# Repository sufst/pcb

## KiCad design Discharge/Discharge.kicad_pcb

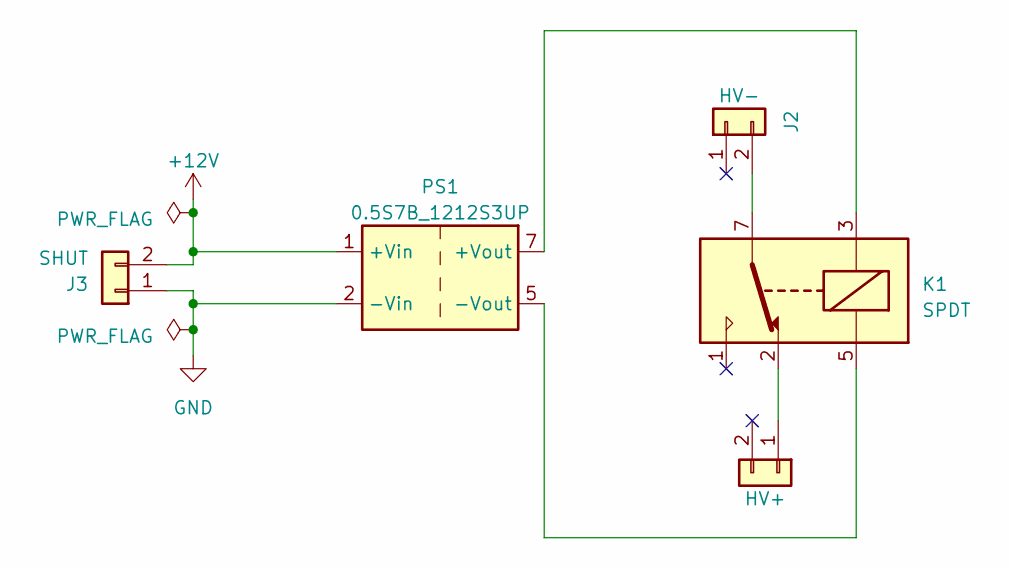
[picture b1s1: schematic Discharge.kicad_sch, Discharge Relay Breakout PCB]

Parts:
J1: HV+; Molex_Micro-Fit_3.0_43650-0200_1x02_P3.00mm_Horizontal
J2: HV-; Molex_Micro-Fit_3.0_43650-0200_1x02_P3.00mm_Horizontal
J3: SHUT; Molex_Micro-Fit_3.0_43650-0215_1x02_P3.00mm_Vertical
K1: SPDT; pickering-67-1-c
PS1: 0.5S7B_1212S3UP

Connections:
+12V: J3.2, PS1.1 (+Vin)
GND: J3.1, PS1.2 (-Vin)
unnamed: J1.1, K1.2
unnamed: J2.2, K1.7
unnamed: K1.3, PS1.7 (+Vout)
unnamed: K1.5, PS1.5 (-Vout)

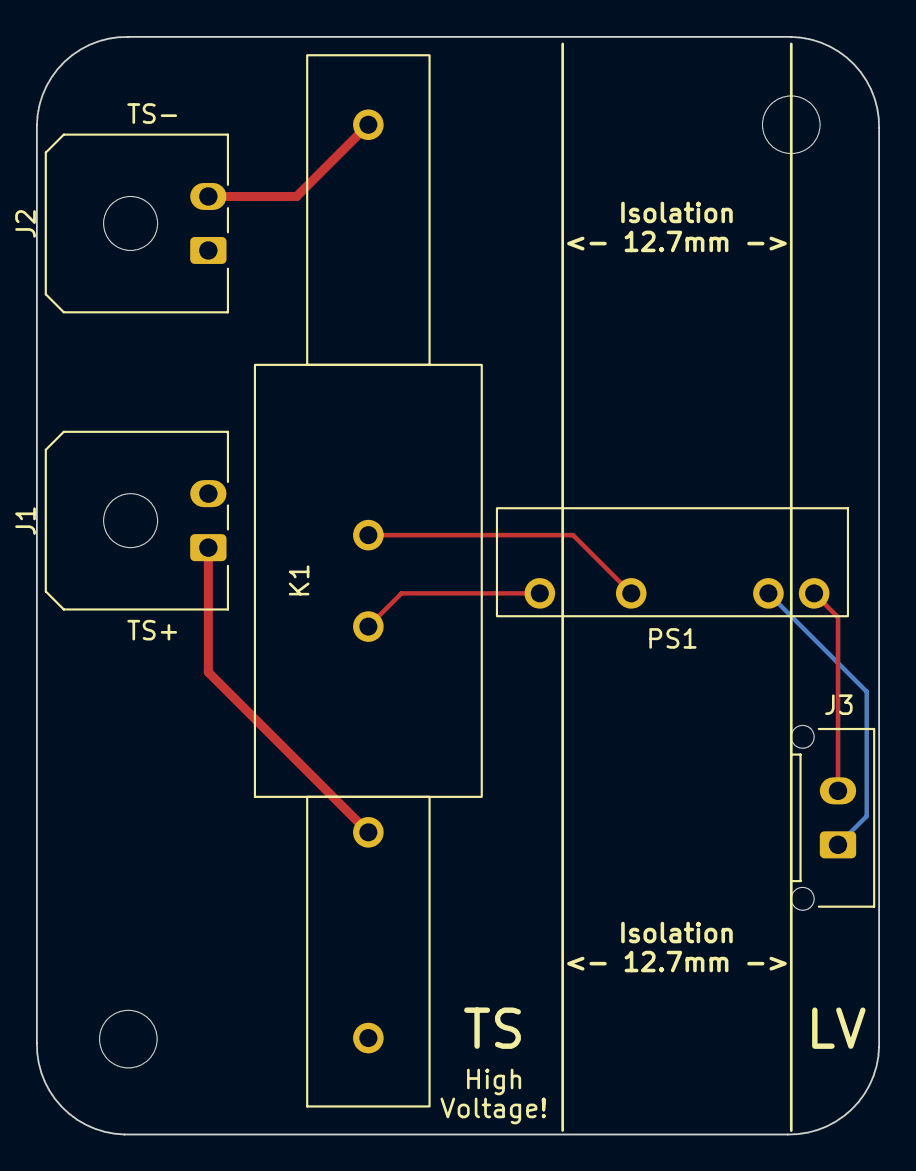
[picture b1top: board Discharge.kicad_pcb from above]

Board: 2 copper layers, 46.8 x 61.0 mm, 5 parts (0 on the bottom side), 6 nets.

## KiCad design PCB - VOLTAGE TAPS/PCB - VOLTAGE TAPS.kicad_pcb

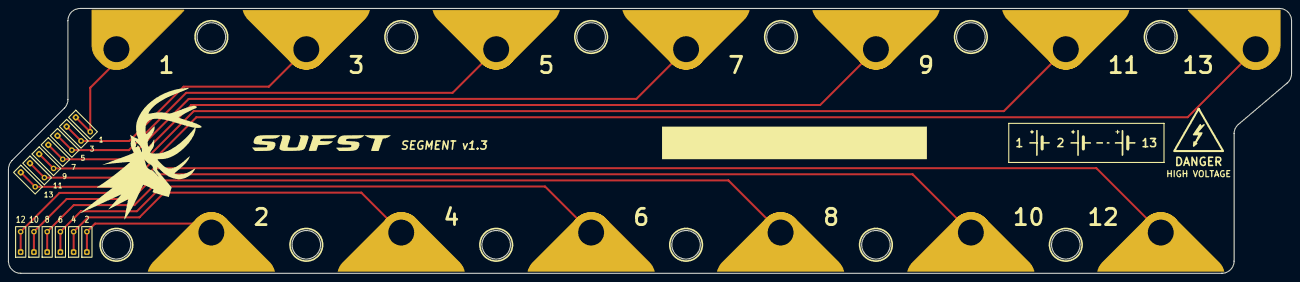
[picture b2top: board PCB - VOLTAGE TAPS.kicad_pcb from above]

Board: 2 copper layers, 314.9 x 65.0 mm, 29 parts (0 on the bottom side), 13 nets.

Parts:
H1, H2, H3: MountingHole; Segment_Thermistor_Tyrap
TP1: VTAP_IN_1; Segment_Voltage_Tap_Positive
TP2: VTAP_IN_2; Segment_Voltage_Tap
TP3: VTAP_IN_3; Segment_Voltage_Tap
TP4: VTAP_IN_4; Segment_Voltage_Tap
TP5: VTAP_IN_5; Segment_Voltage_Tap
TP6: VTAP_IN_6; Segment_Voltage_Tap
TP7: VTAP_IN_7; Segment_Voltage_Tap
TP8: VTAP_IN_8; Segment_Voltage_Tap
TP9: VTAP_IN_9; Segment_Voltage_Tap
TP10: VTAP_IN_10; Segment_Voltage_Tap
TP11: VTAP_IN_11; Segment_Voltage_Tap
TP12: VTAP_IN_12; Segment_Voltage_Tap
TP13: VTAP_OUT_1; 55A_24AWG_Solder
TP14: VTAP_OUT_2; 55A_24AWG_Solder
TP15: VTAP_OUT_3; 55A_24AWG_Solder
TP16: VTAP_OUT_4; 55A_24AWG_Solder
TP17: VTAP_OUT_5; 55A_24AWG_Solder
TP18: VTAP_OUT_6; 55A_24AWG_Solder
TP19: VTAP_OUT_7; 55A_24AWG_Solder
TP20: VTAP_OUT_8; 55A_24AWG_Solder
TP21: VTAP_OUT_9; 55A_24AWG_Solder
TP22: VTAP_OUT_10; 55A_24AWG_Solder
TP23: VTAP_OUT_11; 55A_24AWG_Solder
TP24: VTAP_OUT_12; 55A_24AWG_Solder
TP25: VTAP_IN_13; Segment_Voltage_Tap_Negative
TP26: VTAP_OUT_13; 55A_24AWG_Solder

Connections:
unnamed: TP1.1, TP13.1
unnamed: TP10.1, TP22.1
unnamed: TP11.1, TP23.1
unnamed: TP12.1, TP24.1
unnamed: TP2.1, TP14.1
unnamed: TP3.1, TP15.1
unnamed: TP4.1, TP16.1
unnamed: TP5.1, TP17.1
unnamed: TP6.1, TP18.1
unnamed: TP7.1, TP19.1
unnamed: TP8.1, TP20.1
unnamed: TP9.1, TP21.1
unnamed: TP25.1, TP26.1

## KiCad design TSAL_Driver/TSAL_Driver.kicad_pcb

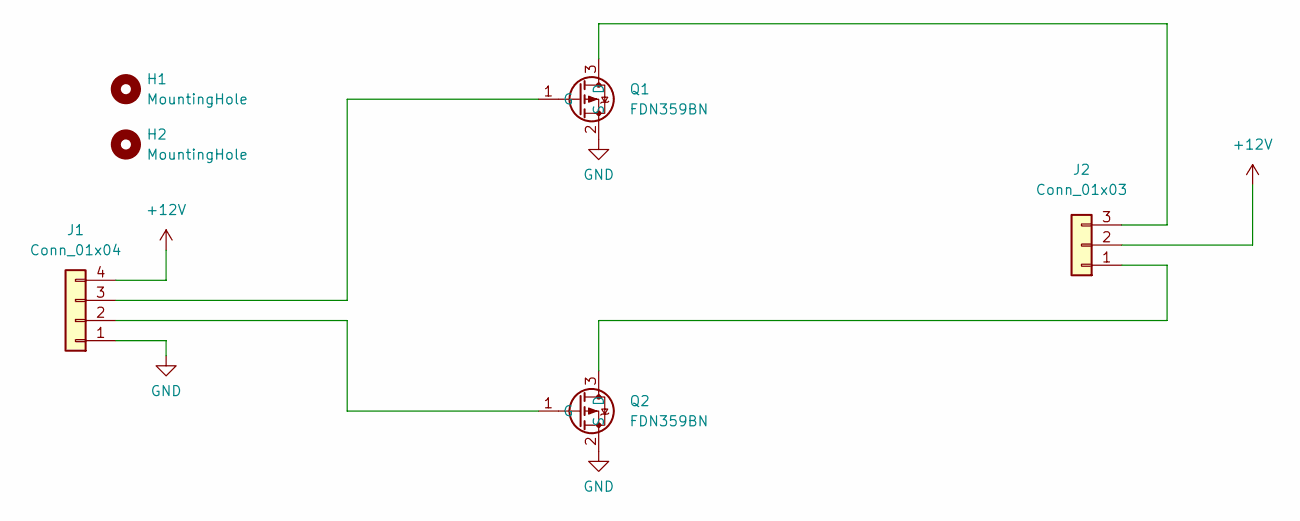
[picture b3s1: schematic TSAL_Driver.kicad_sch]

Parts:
H1, H2: MountingHole; MountingHole_3.2mm_M3
J1: Conn_01x04; Molex_Micro-Fit_3.0_43650-0415_1x04_P3.00mm_Vertical
J2: Conn_01x03; Molex_Micro-Fit_3.0_43650-0315_1x03_P3.00mm_Vertical
Q1, Q2: FDN359BN; SOT-23

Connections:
+12V: J1.4, J2.2
GND: J1.1, Q1.2 (S), Q2.2 (S)
unnamed: J1.2, Q2.1 (G)
unnamed: J1.3, Q1.1 (G)
unnamed: J2.3, Q1.3 (D)
unnamed: J2.1, Q2.3 (D)

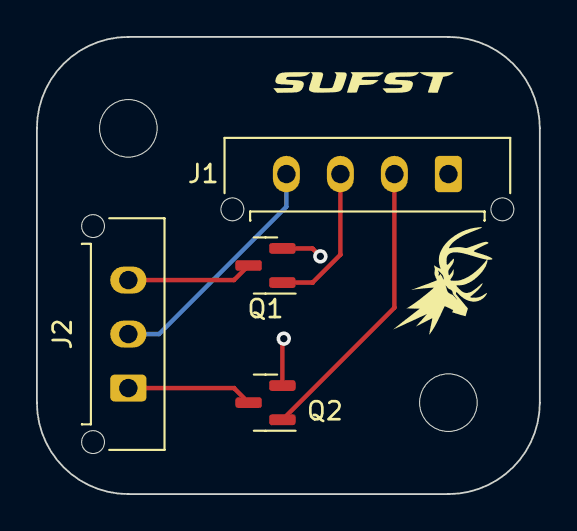
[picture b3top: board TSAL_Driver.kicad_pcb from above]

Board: 2 copper layers, 27.9 x 25.4 mm, 6 parts (0 on the bottom side), 6 nets.

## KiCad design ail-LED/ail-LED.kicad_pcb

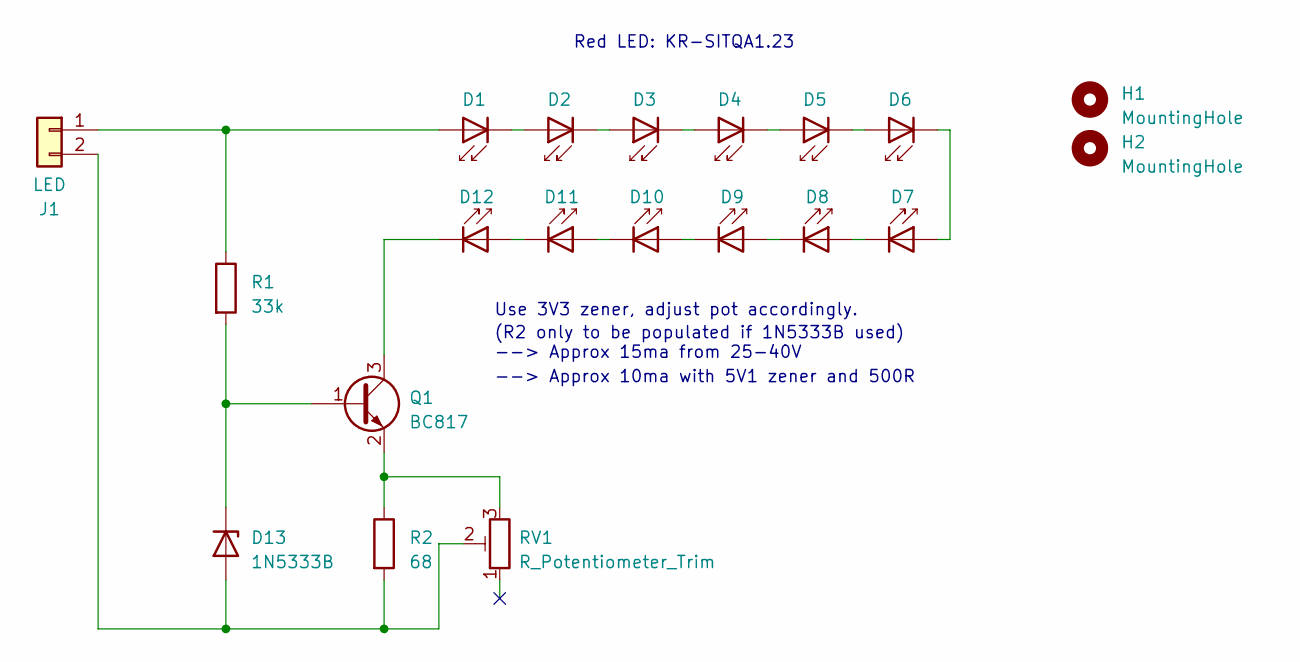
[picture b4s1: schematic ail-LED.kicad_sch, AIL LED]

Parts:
D1, D2, D3, D4, D5, D6, D7, D8, D9, D10, D11, D12: KR-SITQA1.23; KR-SITQA1.23_reflow
D13: 1N5333B; D_SOD-123F
H1, H2: MountingHole; MountingHole_3.2mm_M3
J1: LED; Molex_Micro-Fit_3.0_43650-0214_1x02_P3.00mm_Horizontal
Q1: BC817; SOT-23
R1: 33k; R_0805_2012Metric
R2: 68; R_0805_2012Metric
RV1: R_Potentiometer_Trim; Potentiometer_Bourns_3224J_Horizontal

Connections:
unnamed: D1.2 (A), J1.1, R1.1
unnamed: D1.1 (K), D2.2 (A)
unnamed: D2.1 (K), D3.2 (A)
unnamed: D3.1 (K), D4.2 (A)
unnamed: D4.1 (K), D5.2 (A)
unnamed: D5.1 (K), D6.2 (A)
unnamed: D6.1 (K), D7.2 (A)
unnamed: D7.1 (K), D8.2 (A)
unnamed: D8.1 (K), D9.2 (A)
unnamed: D9.1 (K), D10.2 (A)
unnamed: D10.1 (K), D11.2 (A)
unnamed: D11.1 (K), D12.2 (A)
unnamed: D12.1 (K), Q1.3 (C)
unnamed: D13.2 (A), J1.2, R2.2, RV1.2
unnamed: D13.1 (K), Q1.1 (B), R1.2
unnamed: Q1.2 (E), R2.1, RV1.3

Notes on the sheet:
Red LED: KR-SITQA1.23
Use 3V3 zener, adjust pot accordingly.
(R2 only to be populated if 1N5333B used) --> Approx 15ma from 25-40V
--> Approx 10ma with 5V1 zener and 500R

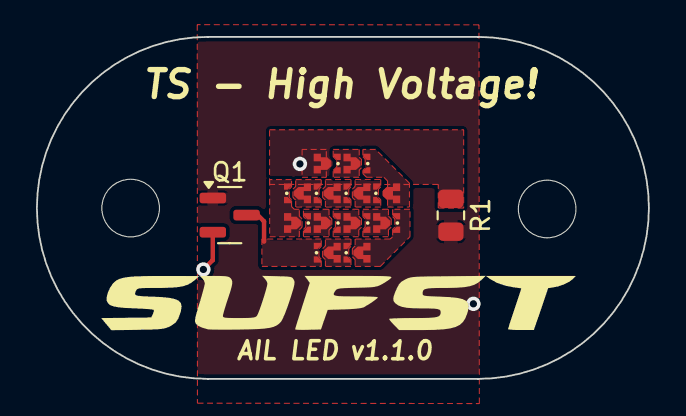
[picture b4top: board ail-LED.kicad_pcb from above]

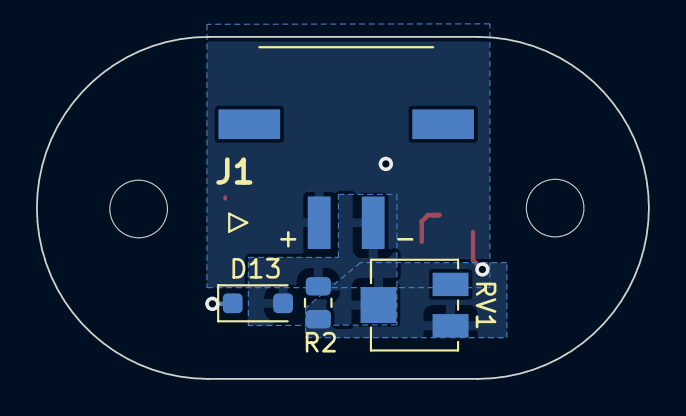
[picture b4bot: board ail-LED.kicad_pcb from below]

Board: 2 copper layers, 34.0 x 19.0 mm, 20 parts (4 on the bottom side), 16 nets.

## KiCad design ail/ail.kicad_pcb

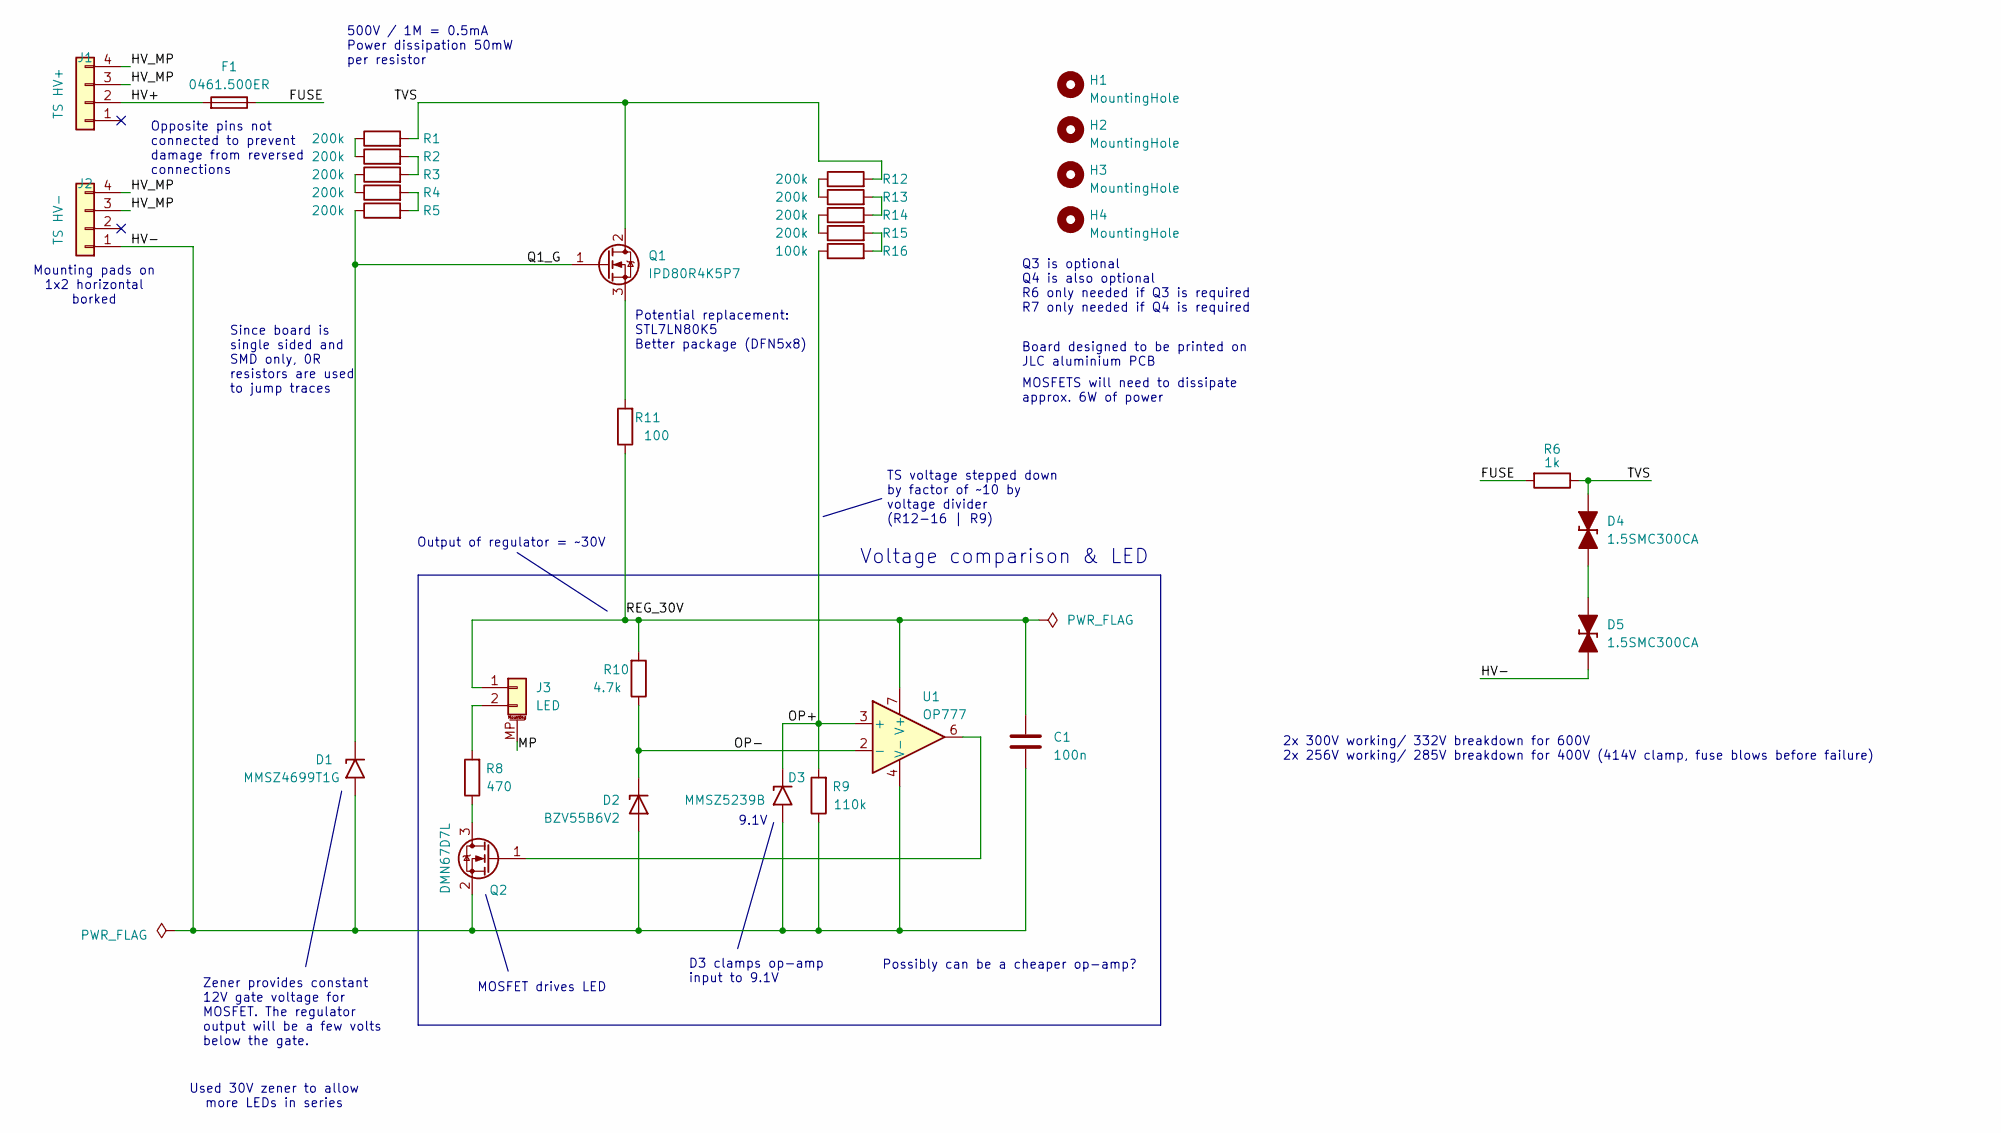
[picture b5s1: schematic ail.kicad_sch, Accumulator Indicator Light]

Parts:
C1: 100n; C_0805_2012Metric_Pad1.18x1.45mm_HandSolder
D1: MMSZ4699T1G; D_SOD-123
D2: BZV55B6V2; D_MiniMELF
D3: MMSZ5239B; D_SOD-123
D4, D5: 1.5SMC300CA; D_SMC_TVS
F1: 0461.500ER; Littelfuse-04611-25ER
H1, H2, H3, H4: MountingHole; MountingHole_4.3mm_M4
J1: TS HV+; Molex_Micro-Fit_3.0_43650-0214_1x02_P3.00mm_Horizontal
J2: TS HV-; Molex_Micro-Fit_3.0_43650-0214_1x02_P3.00mm_Horizontal
J3: LED; Molex_Micro-Fit_3.0_43650-0224_1x02-1MP_P3.00mm_Vertical
Q1: IPD80R4K5P7; TO-252-2
Q2: DMN67D7L; SOT-23
R1, R2, R3, R4, R5, R12, R13, R14, R15: 200k; R_0805_2012Metric_Pad1.20x1.40mm_HandSolder
R6: 1k; R_2512_6332Metric_Pad1.40x3.35mm_HandSolder
R8: 470; R_2512_6332Metric_Pad1.40x3.35mm_HandSolder
R9: 110k; R_0805_2012Metric_Pad1.20x1.40mm_HandSolder
R10: 4.7k; R_0805_2012Metric_Pad1.20x1.40mm_HandSolder
R11: 100; R_0805_2012Metric_Pad1.20x1.40mm_HandSolder
R16: 100k; R_0805_2012Metric_Pad1.20x1.40mm_HandSolder
U1: OP777; SOIC-8_3.9x4.9mm_P1.27mm

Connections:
/FUSE: F1.1, R6.2
/HV+: F1.2, J1.2
/HV-: C1.2, D1.2 (A2), D2.2 (A), D3.2 (A2), D5.1 (K), J2.1, Q2.2 (S), R9.1, U1.4 (V-)
/HV_MP: J1.3, J1.4, J2.3, J2.4
/MP: J3.MP (MountPin)
/OP+: D3.1 (A1), R9.2, R16.1, U1.3 (+)
/OP-: D2.1 (K), R10.1, U1.2 (-)
/Q1_G: D1.1 (A1), Q1.1 (G), R5.1
/REG_30V: C1.1, J3.1, R10.2, R11.1, U1.7 (V+)
/TVS: D4.2 (A), Q1.2 (D), R1.2, R6.1, R12.2
unnamed: D4.1 (K), D5.2 (A)
unnamed: J3.2, R8.2
unnamed: Q1.3 (S), R11.2
unnamed: Q2.3 (D), R8.1
unnamed: Q2.1 (G), U1.6
unnamed: R1.1, R2.1
unnamed: R2.2, R3.2
unnamed: R3.1, R4.1
unnamed: R4.2, R5.2
unnamed: R12.1, R13.1
unnamed: R13.2, R14.2
unnamed: R14.1, R15.1
unnamed: R15.2, R16.2

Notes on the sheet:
Potential replacement: STL7LN80K5 Better package (DFN5x8)
Opposite pins not connected to prevent damage from reversed connections
MOSFET drives LED
TS voltage stepped down by factor of ~10 by voltage divider (R12-16 | R9)
9.1V
500V / 1M = 0.5mA Power dissipation 50mW per resistor
Output of regulator = ~30V
MOSFETS will need to dissipate approx. 6W of power
Possibly can be a cheaper op-amp?
Used 30V zener to allow more LEDs in series
D3 clamps op-amp input to 9.1V
Board designed to be printed on JLC aluminium PCB
Zener provides constant 12V gate voltage for MOSFET. The regulator output will be a few volts below the gate.
Q3 is optional Q4 is also optional R6 only needed if Q3 is required R7 only needed if Q4 is required
2x 300V working/ 332V breakdown for 600V 2x 256V working/ 285V breakdown for 400V (414V clamp, fuse blows before failure)
Since board is single sided and SMD only, 0R resistors are used to jump traces
Voltage comparison & LED
Mounting pads on 1x2 horizontal borked

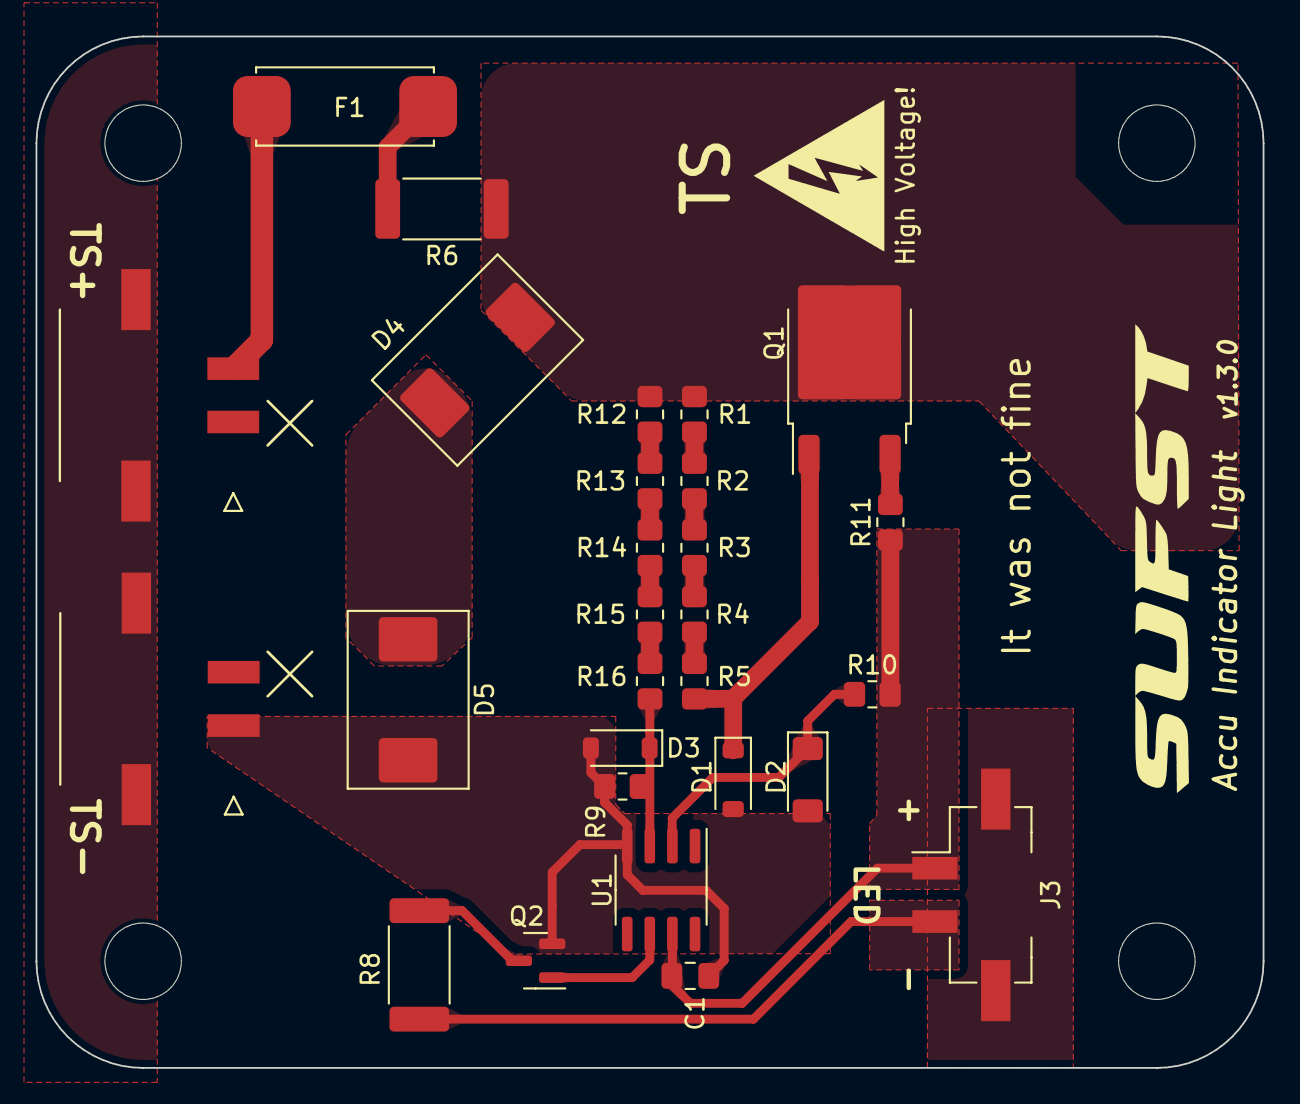
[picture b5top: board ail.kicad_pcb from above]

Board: 2 copper layers, 69.0 x 58.0 mm, 32 parts (0 on the bottom side), 22 nets.

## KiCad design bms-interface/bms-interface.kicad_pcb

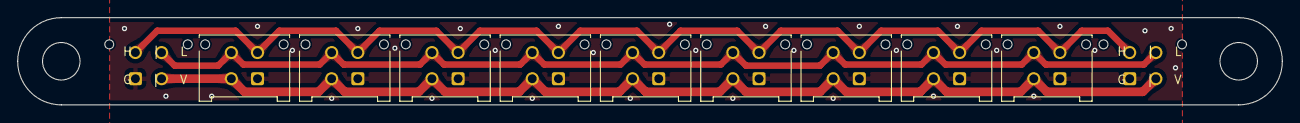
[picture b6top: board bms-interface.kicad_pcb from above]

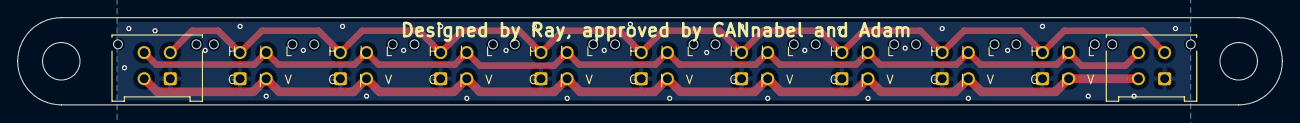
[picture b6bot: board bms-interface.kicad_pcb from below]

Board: 2 copper layers, 145.0 x 10.0 mm, 13 parts (2 on the bottom side), 4 nets.

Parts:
H3, H5: MountingHole; MountingHole_4.3mm_M4
J1: CAN_Upstream; Molex_Micro-Fit_3.0_43045-0412_2x02_P3.00mm_Vertical
J2: CAN_Downstream; Molex_Micro-Fit_3.0_43045-0412_2x02_P3.00mm_Vertical
Segment1, Segment2, Segment3, Segment4, Segment5, Segment6, Segment7, Segment8, Segment9: Molex 43045-0412; Molex_Micro-Fit_3.0_43045-0412_2x02_P3.00mm_Vertical

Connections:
+12V: J1.2, J2.2, Segment1.2, Segment2.2, Segment3.2, Segment4.2, Segment5.2, Segment6.2, Segment7.2, Segment8.2, Segment9.2
/CAN+: J1.3, J2.3, Segment1.3, Segment2.3, Segment3.3, Segment4.3, Segment5.3, Segment6.3, Segment7.3, Segment8.3, Segment9.3
/CAN-: J1.4, J2.4, Segment1.4, Segment2.4, Segment3.4, Segment4.4, Segment5.4, Segment6.4, Segment7.4, Segment8.4, Segment9.4
GND: J1.1, J2.1, Segment1.1, Segment2.1, Segment3.1, Segment4.1, Segment5.1, Segment6.1, Segment7.1, Segment8.1, Segment9.1

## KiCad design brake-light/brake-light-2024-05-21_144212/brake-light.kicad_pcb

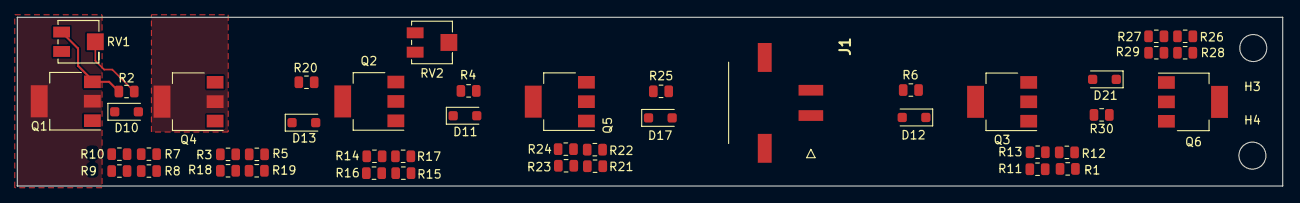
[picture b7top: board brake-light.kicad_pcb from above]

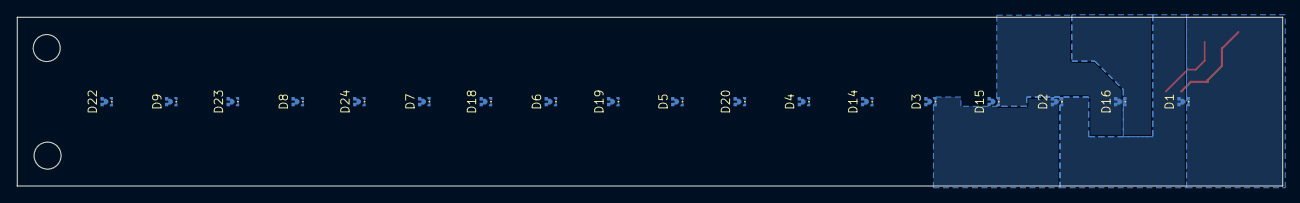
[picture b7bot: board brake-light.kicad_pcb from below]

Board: 2 copper layers, 150.0 x 20.0 mm, 67 parts (18 on the bottom side), 32 nets.

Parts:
D1, D2, D3, D4, D5, D6, D7, D8, D9, D14, D15, D16, D18, D19, D20, D22, D23, D24: KR-SITQA1.23; KR-SITQA1.23_reflow
D10, D11, D12, D13, D17, D21: 1N5333B; D_SOD-123F
H1, H2, H3, H4: MountingHole; MountingHole_3.2mm_M3
J1: LED; Molex_Micro-Fit_3.0_43650-0214_1x02_P3.00mm_Horizontal
Q1, Q2, Q3, Q4, Q5, Q6: BCP56; SOT-223-3_TabPin2
R1, R3, R5, R7, R8, R9, R10, R11, R12, R13, R14, R15, R16, R17, R18, R19, R21, R22, R23, R24, R26, R27, R28, R29: 2.7k; R_0805_2012Metric
R2, R4, R6, R20, R25, R30: 68; R_0805_2012Metric
RV1, RV2: R_Potentiometer_Trim; Potentiometer_Bourns_3224J_Horizontal

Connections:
/LED+: D3.2 (A), D6.2 (A), D9.2 (A), D14.2 (A), D18.2 (A), D22.2 (A), J1.1, R1.1, R3.1, R7.1, R8.1, R12.1, R14.1, R16.1, R18.1, R21.1, R23.1, R26.1, R28.1
/LED-: D10.2 (A), D11.2 (A), D12.2 (A), D13.2 (A), D17.2 (A), D21.2 (A), J1.2, R2.2, R4.2, R6.2, R20.2, R25.2, R30.2, RV1.2, RV2.2
/REG_0: D10.1 (K), D13.1 (K), Q1.1 (B), Q4.1 (B), R5.2, R9.2, R10.2, R19.2
/REG_1: D11.1 (K), D17.1 (K), Q2.1 (B), Q5.1 (B), R15.2, R17.2, R22.2, R24.2
/REG_2: D12.1 (K), D21.1 (K), Q3.1 (B), Q6.1 (B), R11.2, R13.2, R27.2, R29.2
/TRIM_0: Q1.3 (E), Q4.3 (E), R2.1, R20.1, RV1.3, RV2.3
/TRIM_1: Q2.3 (E), Q5.3 (E), R4.1, R25.1
/TRIM_2: Q3.3 (E), Q6.3 (E), R6.1, R30.1
unnamed: D1.2 (A), D2.1 (K)
unnamed: D1.1 (K), Q1.2 (C)
unnamed: D2.2 (A), D3.1 (K)
unnamed: D4.2 (A), D5.1 (K)
unnamed: D4.1 (K), Q2.2 (C)
unnamed: D5.2 (A), D6.1 (K)
unnamed: D7.2 (A), D8.1 (K)
unnamed: D7.1 (K), Q3.2 (C)
unnamed: D8.2 (A), D9.1 (K)
unnamed: D14.1 (K), D15.2 (A)
unnamed: D15.1 (K), D16.2 (A)
unnamed: D16.1 (K), Q4.2 (C)
unnamed: D18.1 (K), D19.2 (A)
unnamed: D19.1 (K), D20.2 (A)
unnamed: D20.1 (K), Q5.2 (C)
unnamed: D22.1 (K), D23.2 (A)
unnamed: D23.1 (K), D24.2 (A)
unnamed: D24.1 (K), Q6.2 (C)
unnamed: R1.2, R11.1, R12.2, R13.1
unnamed: R7.2, R8.2, R9.1, R10.1
unnamed: R14.2, R15.1, R16.2, R17.1
unnamed: R3.2, R5.1, R18.2, R19.1
unnamed: R21.2, R22.1, R23.2, R24.1
unnamed: R26.2, R27.1, R28.2, R29.1
